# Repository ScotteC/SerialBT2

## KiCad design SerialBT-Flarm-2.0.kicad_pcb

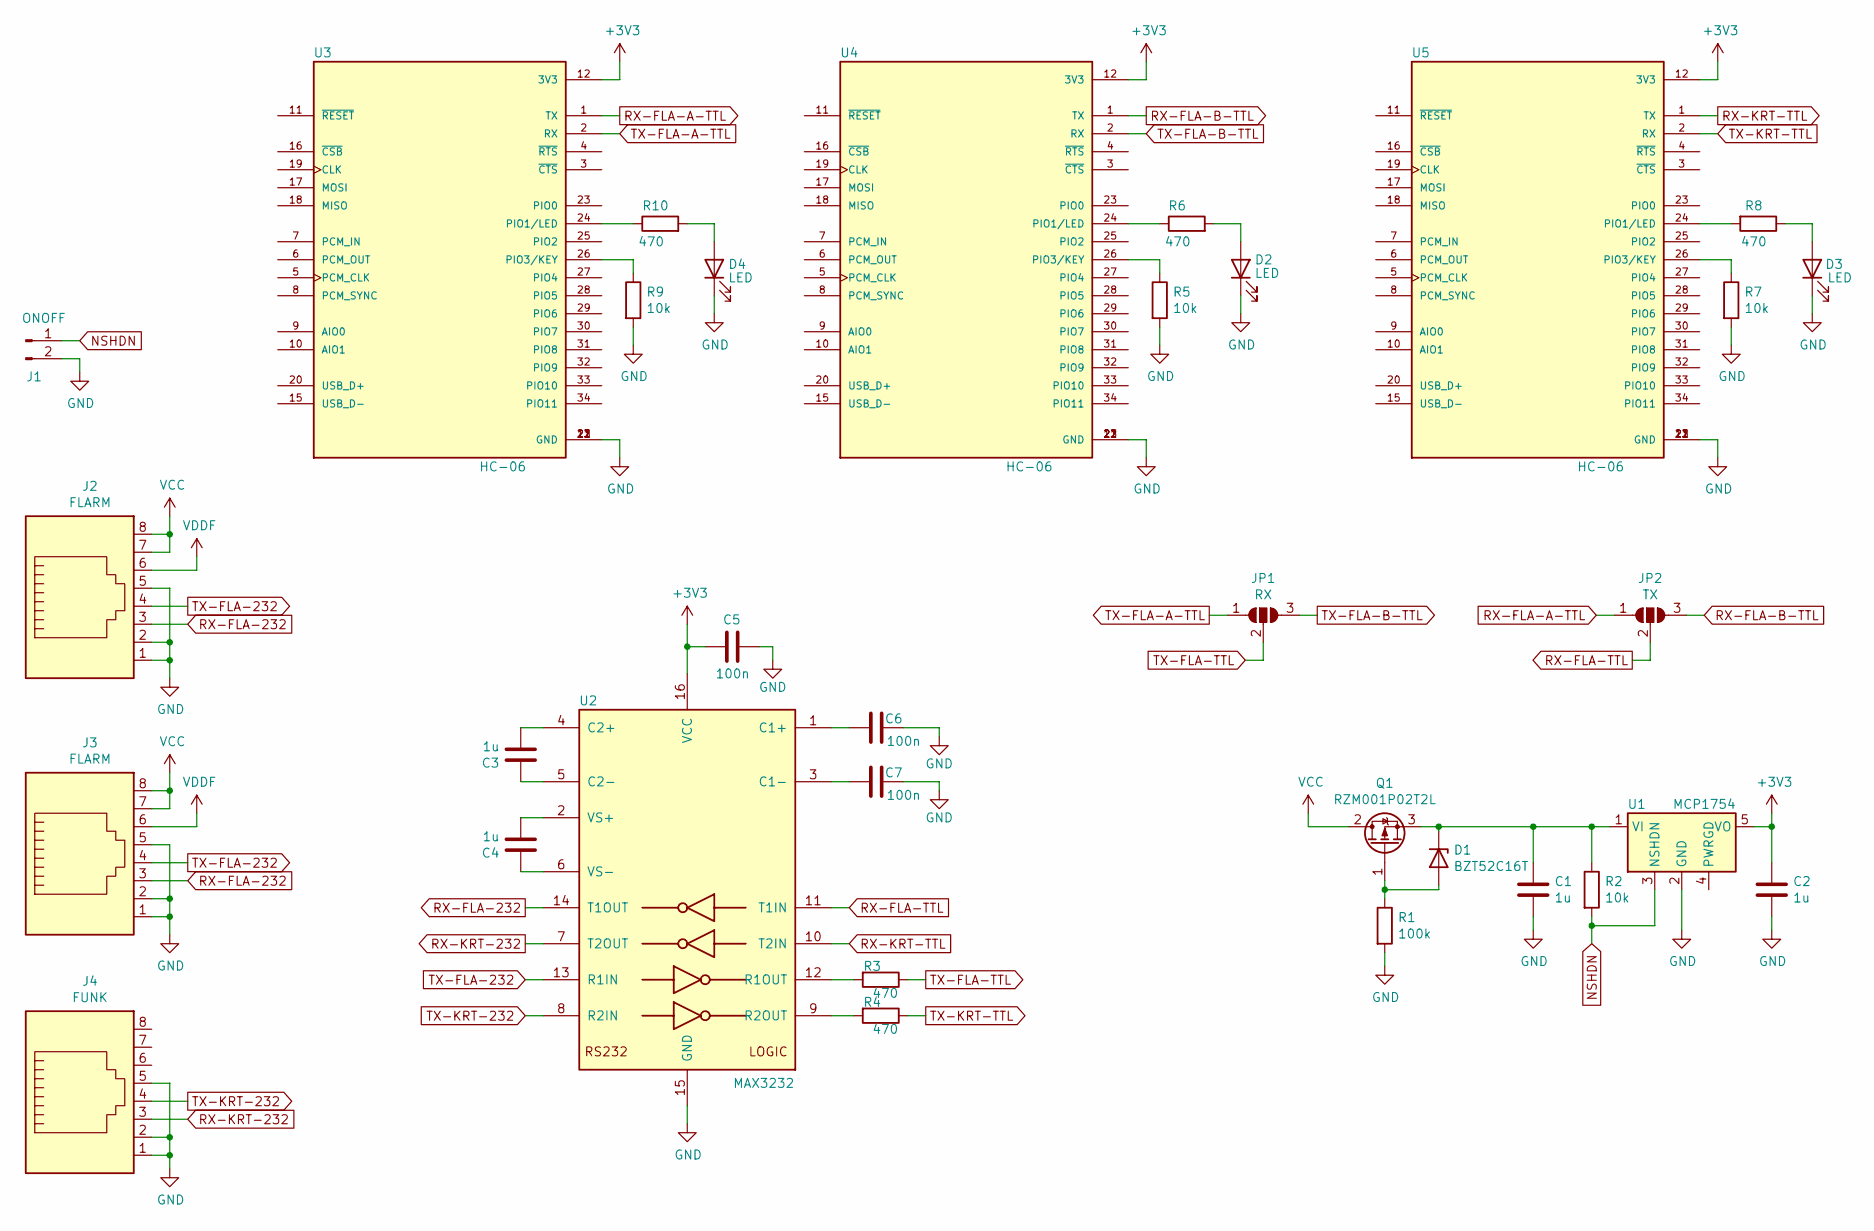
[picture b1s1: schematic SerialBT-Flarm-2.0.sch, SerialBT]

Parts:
C1, C2, C3, C4: 1u; C_0603_1608Metric
C5, C6, C7: 100n; C_0603_1608Metric
D1: BZT52C16T; D_SOD-523
D2, D3, D4: LED; LED_0603_1608Metric
J1: ONOFF; PinHeader_1x02_P2.54mm_Vertical
J2, J3: FLARM; RJ45_Amphenol_54602-x08_Horizontal
J4: FUNK; RJ45_Amphenol_54602-x08_Horizontal
JP1: RX; SolderJumper-3_P1.3mm_Open_RoundedPad1.0x1.5mm_NumberLabels
JP2: TX; SolderJumper-3_P1.3mm_Open_RoundedPad1.0x1.5mm_NumberLabels
Q1: RZM001P02T2L; SOT-723
R1: 100k; R_0603_1608Metric
R2, R5, R7, R9: 10k; R_0603_1608Metric
R3, R4, R6, R8, R10: 470; R_0603_1608Metric
U1: MCP1754; SOT-23-5
U2: MAX3232; TSSOP-16_4.4x5mm_P0.65mm
U3, U4, U5: HC-06; Olimex-HC-06; PARTREV 2.2

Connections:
+3V3: C2.1, C5.1, U1.5 (VO), U2.16 (VCC), U3.12 (3V3), U4.12 (3V3), U5.12 (3V3)
GND: C1.2, C2.2, C5.2, C6.2, C7.2, D2.1 (K), D3.1 (K), D4.1 (K), J1.2, J2.1, J2.2, J2.5, J3.1, J3.2, J3.5, J4.1, J4.2, J4.5, R1.2, R5.2, R7.2, R9.2, U1.2 (GND), U2.15 (GND), U3.13 (GND), U3.21 (GND), U3.22 (GND), U4.13 (GND), U4.21 (GND), U4.22 (GND), U5.13 (GND), U5.21 (GND), U5.22 (GND)
NSHDN: J1.1, R2.2, U1.3 (NSHDN)
unnamed: C1.1, D1.1 (K), Q1.3 (S), R2.1, U1.1 (VI)
unnamed: C3.1, U2.5 (C2-)
unnamed: C3.2, U2.4 (C2+)
unnamed: C4.1, U2.6 (VS-)
unnamed: C4.2, U2.2 (VS+)
unnamed: C6.1, U2.1 (C1+)
unnamed: C7.1, U2.3 (C1-)
unnamed: D1.2 (A), Q1.1 (G), R1.1
unnamed: D2.2 (A), R6.2
unnamed: D3.2 (A), R8.1
unnamed: D4.2 (A), R10.2
unnamed: R3.2, U2.12 (R1OUT)
unnamed: R4.2, U2.9 (R2OUT)
unnamed: R5.1, U4.26 (PIO3/KEY)
unnamed: R6.1, U4.24 (PIO1/LED)
unnamed: R7.1, U5.26 (PIO3/KEY)
unnamed: R8.2, U5.24 (PIO1/LED)
unnamed: R9.1, U3.26 (PIO3/KEY)
unnamed: R10.1, U3.24 (PIO1/LED)
RX-FLA-232: J2.3, J3.3, U2.14 (T1OUT)
RX-FLA-A-TTL: JP2.1 (A), U3.1 (TX)
RX-FLA-B-TTL: JP2.3 (B), U4.1 (TX)
RX-FLA-TTL: JP2.2 (C), U2.11 (T1IN)
RX-KRT-232: J4.3, U2.7 (T2OUT)
RX-KRT-TTL: U2.10 (T2IN), U5.1 (TX)
TX-FLA-232: J2.4, J3.4, U2.13 (R1IN)
TX-FLA-A-TTL: JP1.1 (A), U3.2 (RX)
TX-FLA-B-TTL: JP1.3 (B), U4.2 (RX)
TX-FLA-TTL: JP1.2 (C), R3.1
TX-KRT-232: J4.4, U2.8 (R2IN)
TX-KRT-TTL: R4.1, U5.2 (RX)
VCC: J2.7, J2.8, J3.7, J3.8, Q1.2 (D)
VDDF: J2.6, J3.6

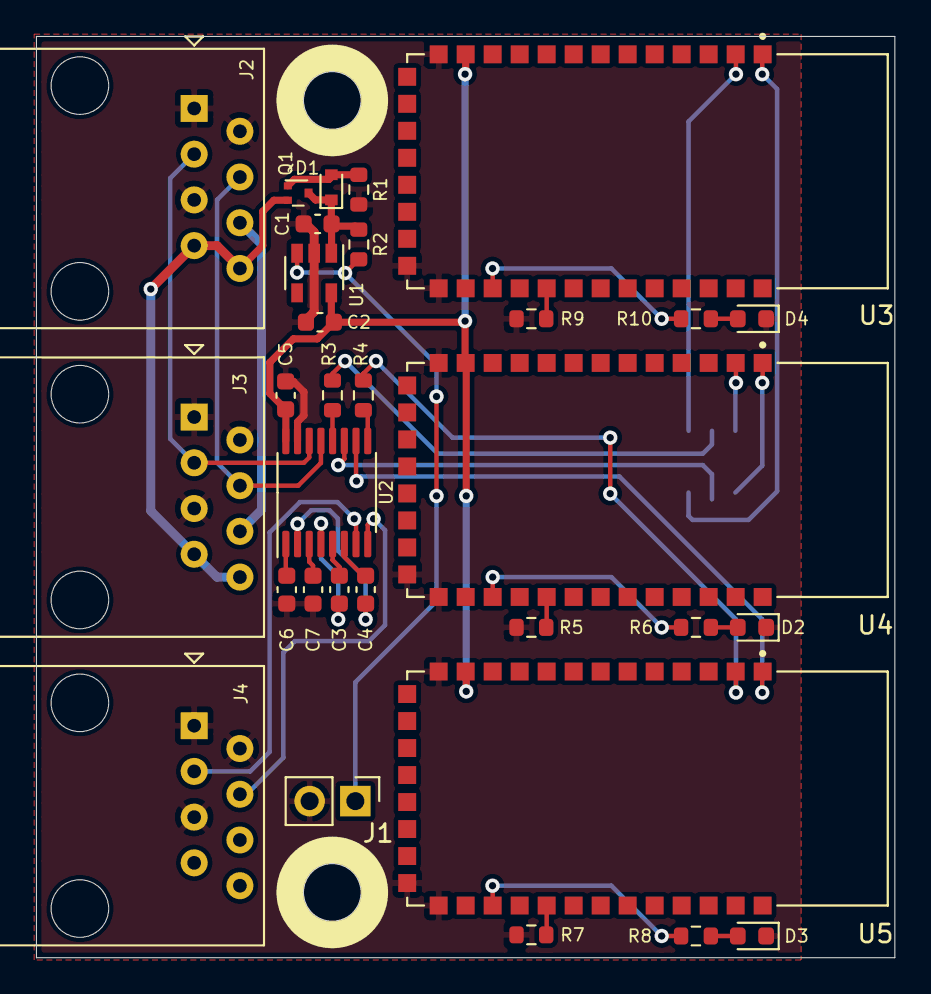
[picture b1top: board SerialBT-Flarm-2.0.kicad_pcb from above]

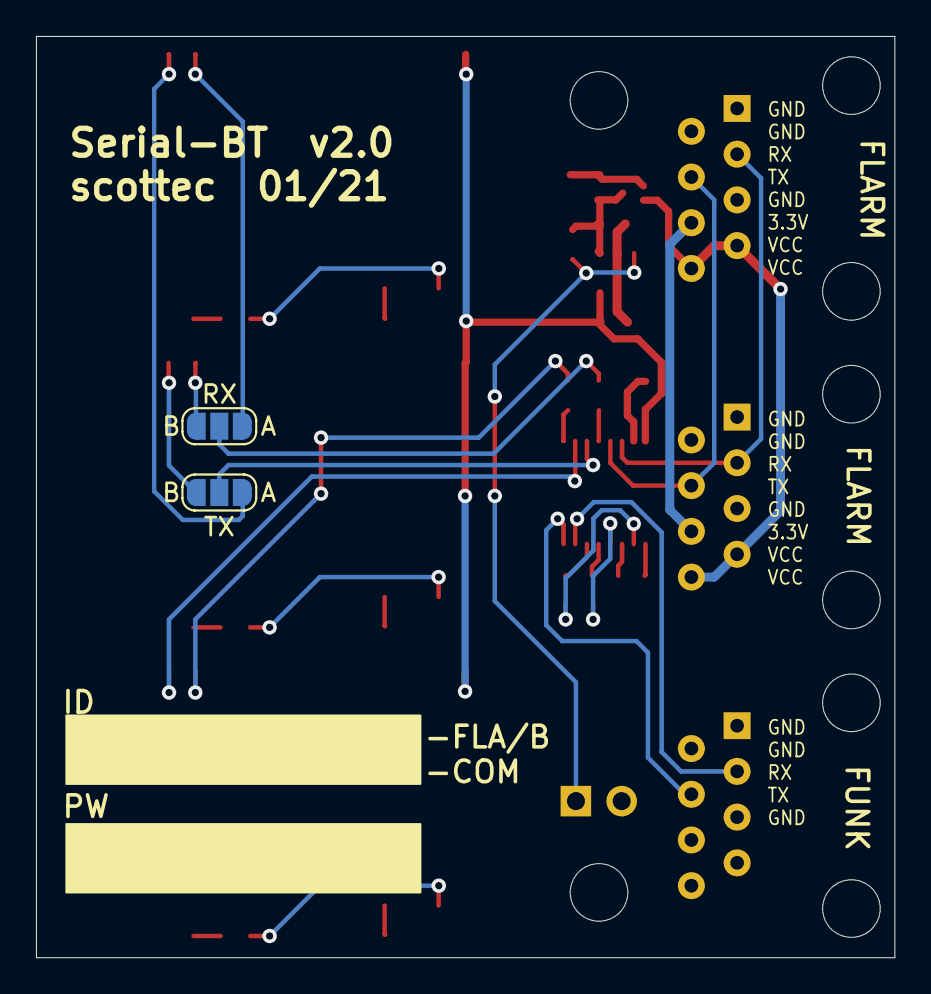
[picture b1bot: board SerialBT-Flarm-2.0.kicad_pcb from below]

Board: 2 copper layers, 47.7 x 51.2 mm, 33 parts (2 on the bottom side), 36 nets.
